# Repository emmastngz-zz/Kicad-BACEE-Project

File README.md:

## Readme  
This repository is a clon to Arduino with:  
* 2 Mbit EEPROM.
* Clock & calendar.
* I2C, SPI, GPIO.  

The original idea is from the user [futureshocked](https://github.com/futureshocked), this project there is too in his [book ](https://techexplorations.com/st/kicad-like-a-pro-2e-support-page/)and [course](https://www.udemy.com/course/kicad-like-a-pro-2e/). If you want to learn how make PCB design in Kicad you will take this course, this is a good option for you. This repository contains: gerber files, pcbnew file, schematic file, and all the project.

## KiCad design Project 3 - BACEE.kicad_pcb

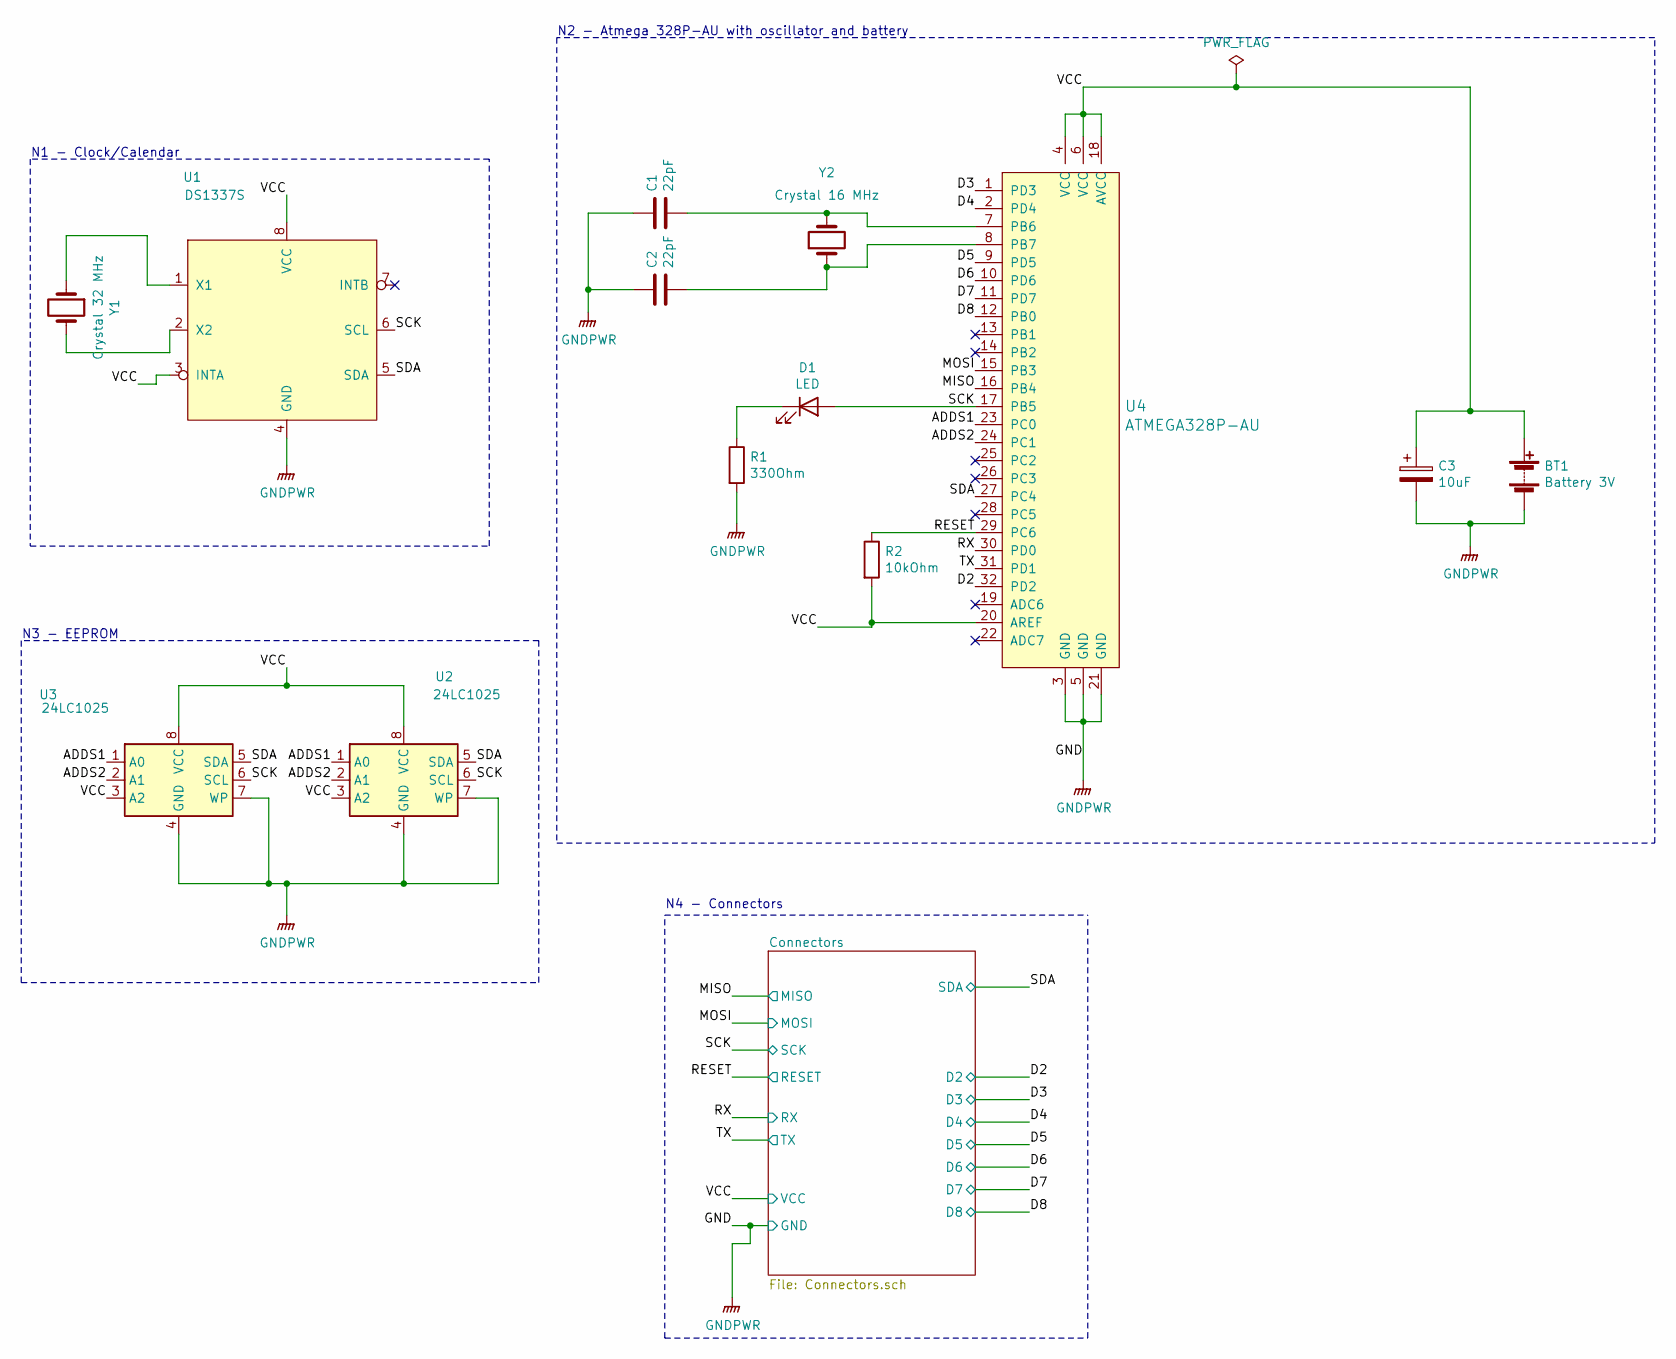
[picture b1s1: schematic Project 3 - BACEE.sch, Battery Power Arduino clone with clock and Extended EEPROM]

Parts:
BT1: Battery 3V; PinHeader_1x02_P2.54mm_Vertical
C1, C2: 22pF; C_0805_2012Metric_Pad1.15x1.40mm_HandSolder
C3: 10uF; C_0805_2012Metric_Pad1.15x1.40mm_HandSolder
D1: LED; LED_0805_2012Metric_Pad1.15x1.40mm_HandSolder
R1: 330Ohm; R_0805_2012Metric_Pad1.15x1.40mm_HandSolder
R2: 10kOhm; R_0805_2012Metric_Pad1.15x1.40mm_HandSolder
U1: DS1337S; SO-8_5.3x6.2mm_P1.27mm
U2, U3: 24LC1025; SOIJ-8_5.3x5.3mm_P1.27mm
U4: ATMEGA328P-AU; TQFP-32_7x7mm; MPN ATMEGA328P-AU; Digi-Key_PN ATMEGA328P-AU-ND
Y1: Crystal 32 MHz; Crystal_SMD_MicroCrystal_CC7V-T1A-2Pin_3.2x1.5mm
Y2: Crystal 16 MHz; Crystal_SMD_5032-2Pin_5.0x3.2mm_HandSoldering

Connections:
/ADDS1: U2.1 (A0), U3.1 (A0), U4.23 (PC0)
/ADDS2: U2.2 (A1), U3.2 (A1), U4.24 (PC1)
/D2: U4.32 (PD2); also elsewhere on the board
/D3: U4.1 (PD3); also elsewhere on the board
/D4: U4.2 (PD4); also elsewhere on the board
/D5: U4.9 (PD5); also elsewhere on the board
/D6: U4.10 (PD6); also elsewhere on the board
/D7: U4.11 (PD7); also elsewhere on the board
/D8: U4.12 (PB0); also elsewhere on the board
/MISO: U4.16 (PB4); also elsewhere on the board
/MOSI: U4.15 (PB3); also elsewhere on the board
/RESET: R2.1, U4.29 (PC6); also elsewhere on the board
/RX: U4.30 (PD0); also elsewhere on the board
/SCK: D1.2 (A), U1.6 (SCL), U2.6 (SCL), U3.6 (SCL), U4.17 (PB5); also elsewhere on the board
/SDA: U1.5 (SDA), U2.5 (SDA), U3.5 (SDA), U4.27 (PC4); also elsewhere on the board
/TX: U4.31 (PD1); also elsewhere on the board
/VCC: BT1.1 (+), C3.1, R2.2, U1.3 (INTA), U1.8 (VCC), U2.3 (A2), U2.8 (VCC), U3.3 (A2), U3.8 (VCC), U4.4 (VCC), U4.6 (VCC), U4.18 (AVCC), U4.20 (AREF); also elsewhere on the board
GNDPWR: BT1.2 (-), C1.1, C2.1, C3.2, R1.2, U1.4 (GND), U2.4 (GND), U2.7 (WP), U3.4 (GND), U3.7 (WP), U4.3 (GND), U4.5 (GND), U4.21 (GND); also elsewhere on the board
unnamed: C1.2, U4.7 (PB6), Y2.2
unnamed: C2.2, U4.8 (PB7), Y2.1
unnamed: D1.1 (K), R1.1
unnamed: U1.1 (X1), Y1.1
unnamed: U1.2 (X2), Y1.2

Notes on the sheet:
N1 - Clock/Calendar
N3 - EEPROM
N2 - Atmega 328P-AU with oscillator and battery
N4 - Connectors

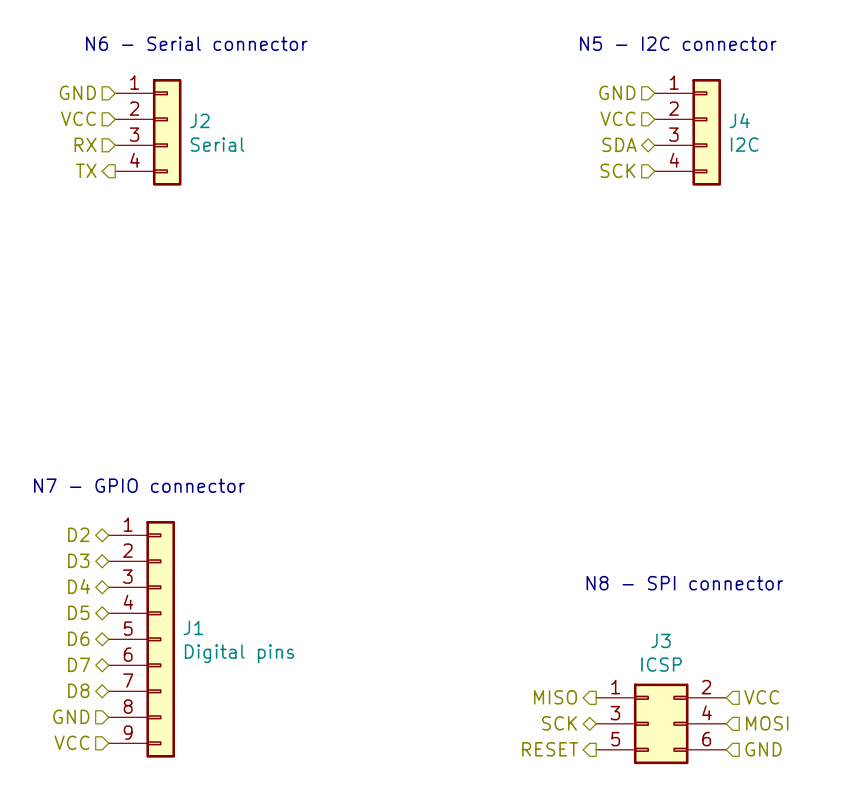
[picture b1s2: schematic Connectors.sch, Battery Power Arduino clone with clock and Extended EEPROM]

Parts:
J1: Digital pins; PinSocket_1x09_P2.54mm_Vertical
J2: Serial; PinSocket_1x04_P2.54mm_Vertical
J3: ICSP; PinSocket_2x03_P2.54mm_Vertical
J4: I2C; PinSocket_1x04_P2.54mm_Vertical

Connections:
/D2: J1.1; also elsewhere on the board
/D3: J1.2; also elsewhere on the board
/D4: J1.3; also elsewhere on the board
/D5: J1.4; also elsewhere on the board
/D6: J1.5; also elsewhere on the board
/D7: J1.6; also elsewhere on the board
/D8: J1.7; also elsewhere on the board
/MISO: J3.1; also elsewhere on the board
/MOSI: J3.4; also elsewhere on the board
/RESET: J3.5; also elsewhere on the board
/RX: J2.3; also elsewhere on the board
/SCK: J3.3, J4.4; also elsewhere on the board
/SDA: J4.3; also elsewhere on the board
/TX: J2.4; also elsewhere on the board
/VCC: J1.9, J2.2, J3.2, J4.2; also elsewhere on the board
GNDPWR: J1.8, J2.1, J3.6, J4.1; also elsewhere on the board

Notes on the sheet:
N6 - Serial connector
N5 - I2C connector
N7 - GPIO connector
N8 - SPI connector

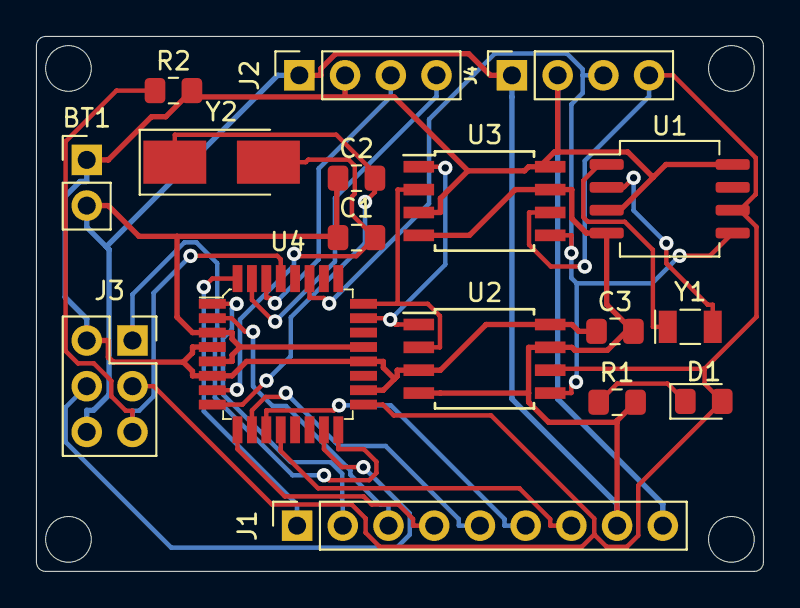
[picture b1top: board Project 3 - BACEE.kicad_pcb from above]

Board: 4 copper layers, 40.4 x 29.7 mm, 17 parts (0 on the bottom side), 23 nets.

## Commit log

2020-07-11 First commit.
2020-07-11 Setup the title block in the schematic sheet.
2020-07-13 Create new child scheet, added project symbols.
2020-07-13 Added symbol for ATMEGA328P-AU
2020-07-13 Added clock IC custom symbol
2020-07-15 Added missing crystals.
2020-07-15 Arrenged symbols.
2020-07-15 Annotated.
2020-07-15 Completed association and added component values.
2020-07-16 Completed wiring in connectors sheet
2020-07-17 Completed wiring in root sheet
2020-07-17 Added power flag symbol.
2020-07-17 Added functional block descriptions.
2020-07-17 Created netlist file.
2020-07-17 Started work in PCBnew.
2020-07-18 Set design rules.
2020-07-19 Placement complete.
2020-07-19 Created outline and mounting holes.
2020-07-21 Fully routed board in two layers.
2020-07-21 Created copper filled area for 2-layer board and 4-layer board.
2020-07-21 Completed work in silkscreen layers.
2020-07-21 Added the gerber files.
2020-07-21 Added README.md and Gerber files.
